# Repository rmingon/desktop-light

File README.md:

# Desktop Light

## desktop light with micro usb programming usb and extendable light

### features
* ESP32
* WS2812b
* RTC
* 3 programmable buttons
* CH310 usb programming
* Jack connector 5V

### Real

### 3d

### pcb

### schematic

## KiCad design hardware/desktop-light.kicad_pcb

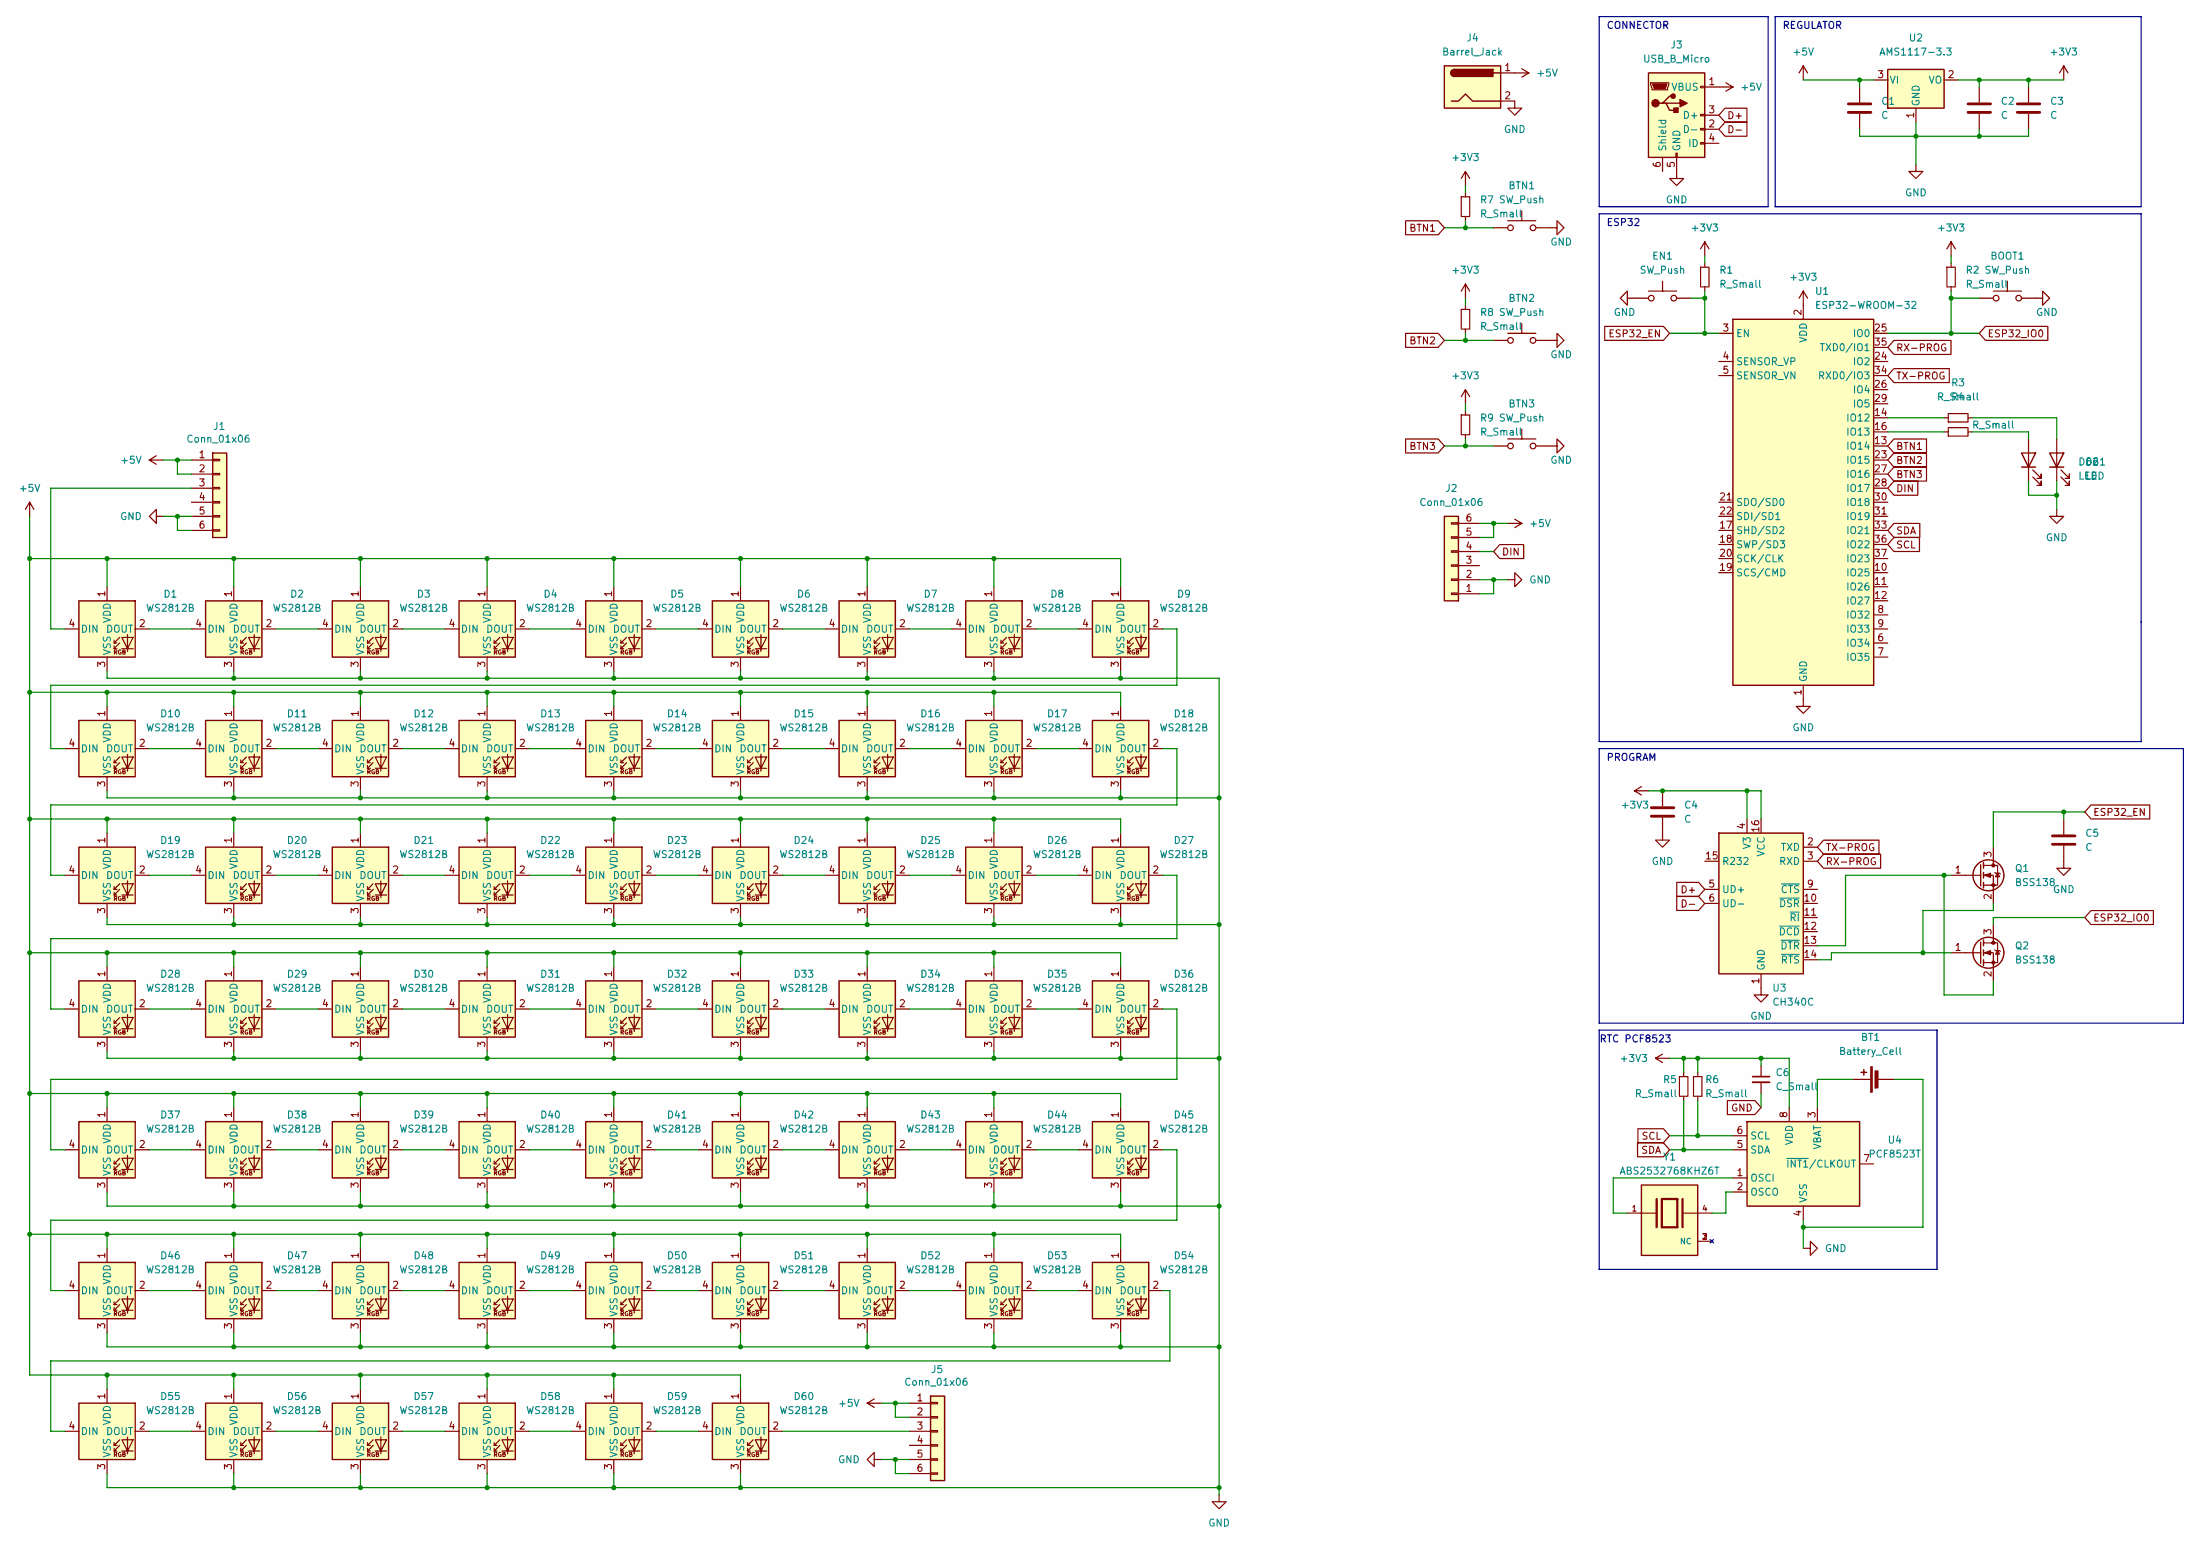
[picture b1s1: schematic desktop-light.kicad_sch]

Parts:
BOOT1: SW_Push; SW_SPST_FSMSM
BT1: Battery_Cell; BatteryHolder_LINX_BAT-HLD-012-SMT
BTN1, BTN2, BTN3: SW_Push; SW_SPST_FSMSM
C1, C2, C3, C4, C5: C; C_0603_1608Metric
C6: C_Small; C_0603_1608Metric
D1, D2, D3, D4, D5, D6, D7, D8, D9, D10, D11, D12, D13, D14, D15, D16, D17, D18, D19, D20, D21, D22, D23, D24, D25, D26, D27, D28, D29, D30, D31, D32, D33, D34, D35, D36, D37, D38, D39, D40, D41, D42, D43, D44, D45, D46, D47, D48, D49, D50, D51, D52, D53, D54, D55, D56, D57, D58, D59, D60: WS2812B; LED_WS2812B_PLCC4_5.0x5.0mm_P3.2mm
D61, D62: LED; LED_0603_1608Metric
EN1: SW_Push; SW_SPST_FSMSM
J1, J2, J5: Conn_01x06; JST_SH_BM06B-SRSS-TB_1x06-1MP_P1.00mm_Vertical
J3: USB_B_Micro; USB_Micro-B_Molex-105017-0001
J4: Barrel_Jack; BarrelJack_Wuerth_6941xx301002
Q1, Q2: BSS138; SOT-23
R1, R2, R3, R4, R5, R6, R7, R8, R9: R_Small; R_0603_1608Metric
U1: ESP32-WROOM-32
U2: AMS1117-3.3; SOT-223-3_TabPin2
U3: CH340C; SOIC-16_3.9x9.9mm_P1.27mm
U4: PCF8523T; SOIC-8_3.9x4.9mm_P1.27mm
Y1: ABS2532768KHZ6T; Crystal_SMD_Abracon_ABS25-4Pin_8.0x3.8mm; PARTREV 43738

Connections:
+3V3: C2.1, C3.1, C4.1, C6.1, R1.1, R2.1, R5.1, R6.1, R7.1, R8.1, R9.1, U1.2 (VDD), U2.2 (VO), U3.4 (V3), U3.16 (VCC), U4.8 (VDD)
+5V: C1.1, D1.1 (VDD), D2.1 (VDD), D3.1 (VDD), D4.1 (VDD), D5.1 (VDD), D6.1 (VDD), D7.1 (VDD), D8.1 (VDD), D9.1 (VDD), D10.1 (VDD), D11.1 (VDD), D12.1 (VDD), D13.1 (VDD), D14.1 (VDD), D15.1 (VDD), D16.1 (VDD), D17.1 (VDD), D18.1 (VDD), D19.1 (VDD), D20.1 (VDD), D21.1 (VDD), D22.1 (VDD), D23.1 (VDD), D24.1 (VDD), D25.1 (VDD), D26.1 (VDD), D27.1 (VDD), D28.1 (VDD), D29.1 (VDD), D30.1 (VDD), D31.1 (VDD), D32.1 (VDD), D33.1 (VDD), D34.1 (VDD), D35.1 (VDD), D36.1 (VDD), D37.1 (VDD), D38.1 (VDD), D39.1 (VDD), D40.1 (VDD), D41.1 (VDD), D42.1 (VDD), D43.1 (VDD), D44.1 (VDD), D45.1 (VDD), D46.1 (VDD), D47.1 (VDD), D48.1 (VDD), D49.1 (VDD), D50.1 (VDD), D51.1 (VDD), D52.1 (VDD), D53.1 (VDD), D54.1 (VDD), D55.1 (VDD), D56.1 (VDD), D57.1 (VDD), D58.1 (VDD), D59.1 (VDD), D60.1 (VDD), J1.1, J1.2, J2.5, J2.6, J3.1 (VBUS), J4.1, J5.1, J5.2, U2.3 (VI)
BTN1: BTN1.1, R7.2, U1.13 (IO14)
BTN2: BTN2.1, R8.2, U1.23 (IO15)
BTN3: BTN3.1, R9.2, U1.27 (IO16)
D+: J3.3 (D+), U3.5 (UD+)
D-: J3.2 (D-), U3.6 (UD-)
DIN: J2.4, U1.28 (IO17)
ESP32_EN: C5.1, EN1.2, Q1.3 (D), R1.2, U1.3 (EN)
ESP32_IO0: BOOT1.1, Q2.3 (D), R2.2, U1.25 (IO0)
GND: BOOT1.2, BT1.2 (-), BTN1.2, BTN2.2, BTN3.2, C1.2, C2.2, C3.2, C4.2, C5.2, C6.2, D1.3 (VSS), D2.3 (VSS), D3.3 (VSS), D4.3 (VSS), D5.3 (VSS), D6.3 (VSS), D7.3 (VSS), D8.3 (VSS), D9.3 (VSS), D10.3 (VSS), D11.3 (VSS), D12.3 (VSS), D13.3 (VSS), D14.3 (VSS), D15.3 (VSS), D16.3 (VSS), D17.3 (VSS), D18.3 (VSS), D19.3 (VSS), D20.3 (VSS), D21.3 (VSS), D22.3 (VSS), D23.3 (VSS), D24.3 (VSS), D25.3 (VSS), D26.3 (VSS), D27.3 (VSS), D28.3 (VSS), D29.3 (VSS), D30.3 (VSS), D31.3 (VSS), D32.3 (VSS), D33.3 (VSS), D34.3 (VSS), D35.3 (VSS), D36.3 (VSS), D37.3 (VSS), D38.3 (VSS), D39.3 (VSS), D40.3 (VSS), D41.3 (VSS), D42.3 (VSS), D43.3 (VSS), D44.3 (VSS), D45.3 (VSS), D46.3 (VSS), D47.3 (VSS), D48.3 (VSS), D49.3 (VSS), D50.3 (VSS), D51.3 (VSS), D52.3 (VSS), D53.3 (VSS), D54.3 (VSS), D55.3 (VSS), D56.3 (VSS), D57.3 (VSS), D58.3 (VSS), D59.3 (VSS), D60.3 (VSS), D61.1 (K), D62.1 (K), EN1.1, J1.5, J1.6, J2.1, J2.2, J3.5 (GND), J4.2, J5.5, J5.6, U1.1 (GND), U1.15 (GND), U1.38 (GND), U1.39 (GND), U2.1 (GND), U3.1 (GND), U4.4 (VSS)
unnamed: BT1.1 (+), U4.3 (VBAT)
unnamed: D1.4 (DIN), J1.3
unnamed: D1.2 (DOUT), D2.4 (DIN)
unnamed: D2.2 (DOUT), D3.4 (DIN)
unnamed: D3.2 (DOUT), D4.4 (DIN)
unnamed: D4.2 (DOUT), D5.4 (DIN)
unnamed: D5.2 (DOUT), D6.4 (DIN)
unnamed: D6.2 (DOUT), D7.4 (DIN)
unnamed: D7.2 (DOUT), D8.4 (DIN)
unnamed: D8.2 (DOUT), D9.4 (DIN)
unnamed: D9.2 (DOUT), D10.4 (DIN)
unnamed: D10.2 (DOUT), D11.4 (DIN)
unnamed: D11.2 (DOUT), D12.4 (DIN)
unnamed: D12.2 (DOUT), D13.4 (DIN)
unnamed: D13.2 (DOUT), D14.4 (DIN)
unnamed: D14.2 (DOUT), D15.4 (DIN)
unnamed: D15.2 (DOUT), D16.4 (DIN)
unnamed: D16.2 (DOUT), D17.4 (DIN)
unnamed: D17.2 (DOUT), D18.4 (DIN)
unnamed: D18.2 (DOUT), D19.4 (DIN)
unnamed: D19.2 (DOUT), D20.4 (DIN)
unnamed: D20.2 (DOUT), D21.4 (DIN)
unnamed: D21.2 (DOUT), D22.4 (DIN)
unnamed: D22.2 (DOUT), D23.4 (DIN)
unnamed: D23.2 (DOUT), D24.4 (DIN)
unnamed: D24.2 (DOUT), D25.4 (DIN)
unnamed: D25.2 (DOUT), D26.4 (DIN)
unnamed: D26.2 (DOUT), D27.4 (DIN)
unnamed: D27.2 (DOUT), D28.4 (DIN)
unnamed: D28.2 (DOUT), D29.4 (DIN)
unnamed: D29.2 (DOUT), D30.4 (DIN)
unnamed: D30.2 (DOUT), D31.4 (DIN)
unnamed: D31.2 (DOUT), D32.4 (DIN)
unnamed: D32.2 (DOUT), D33.4 (DIN)
unnamed: D33.2 (DOUT), D34.4 (DIN)
unnamed: D34.2 (DOUT), D35.4 (DIN)
unnamed: D35.2 (DOUT), D36.4 (DIN)
unnamed: D36.2 (DOUT), D37.4 (DIN)
unnamed: D37.2 (DOUT), D38.4 (DIN)
unnamed: D38.2 (DOUT), D39.4 (DIN)
unnamed: D39.2 (DOUT), D40.4 (DIN)
unnamed: D40.2 (DOUT), D41.4 (DIN)
unnamed: D41.2 (DOUT), D42.4 (DIN)
unnamed: D42.2 (DOUT), D43.4 (DIN)
unnamed: D43.2 (DOUT), D44.4 (DIN)
unnamed: D44.2 (DOUT), D45.4 (DIN)
unnamed: D45.2 (DOUT), D46.4 (DIN)
unnamed: D46.2 (DOUT), D47.4 (DIN)
unnamed: D47.2 (DOUT), D48.4 (DIN)
unnamed: D48.2 (DOUT), D49.4 (DIN)
unnamed: D49.2 (DOUT), D50.4 (DIN)
unnamed: D50.2 (DOUT), D51.4 (DIN)
unnamed: D51.2 (DOUT), D52.4 (DIN)
unnamed: D52.2 (DOUT), D53.4 (DIN)
unnamed: D53.2 (DOUT), D54.4 (DIN)
unnamed: D54.2 (DOUT), D55.4 (DIN)
unnamed: D55.2 (DOUT), D56.4 (DIN)
unnamed: D56.2 (DOUT), D57.4 (DIN)
unnamed: D57.2 (DOUT), D58.4 (DIN)
unnamed: D58.2 (DOUT), D59.4 (DIN)
unnamed: D59.2 (DOUT), D60.4 (DIN)
unnamed: D60.2 (DOUT), J5.3
unnamed: D61.2 (A), R4.2
unnamed: D62.2 (A), R3.2
unnamed: Q1.1 (G), Q2.2 (S), U3.13 (~DTR)
unnamed: Q1.2 (S), Q2.1 (G), U3.14 (~RTS)
unnamed: R3.1, U1.14 (IO12)
unnamed: R4.1, U1.16 (IO13)
unnamed: U4.1 (OSCI), Y1.1
unnamed: U4.2 (OSCO), Y1.4
RX-PROG: U1.35 (TXD0/IO1), U3.3 (RXD)
SCL: R6.2, U1.36 (IO22), U4.6 (SCL)
SDA: R5.2, U1.33 (IO21), U4.5 (SDA)
TX-PROG: U1.34 (RXD0/IO3), U3.2 (TXD)

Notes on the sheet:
ESP32
REGULATOR
CONNECTOR
PROGRAM
RTC PCF8523

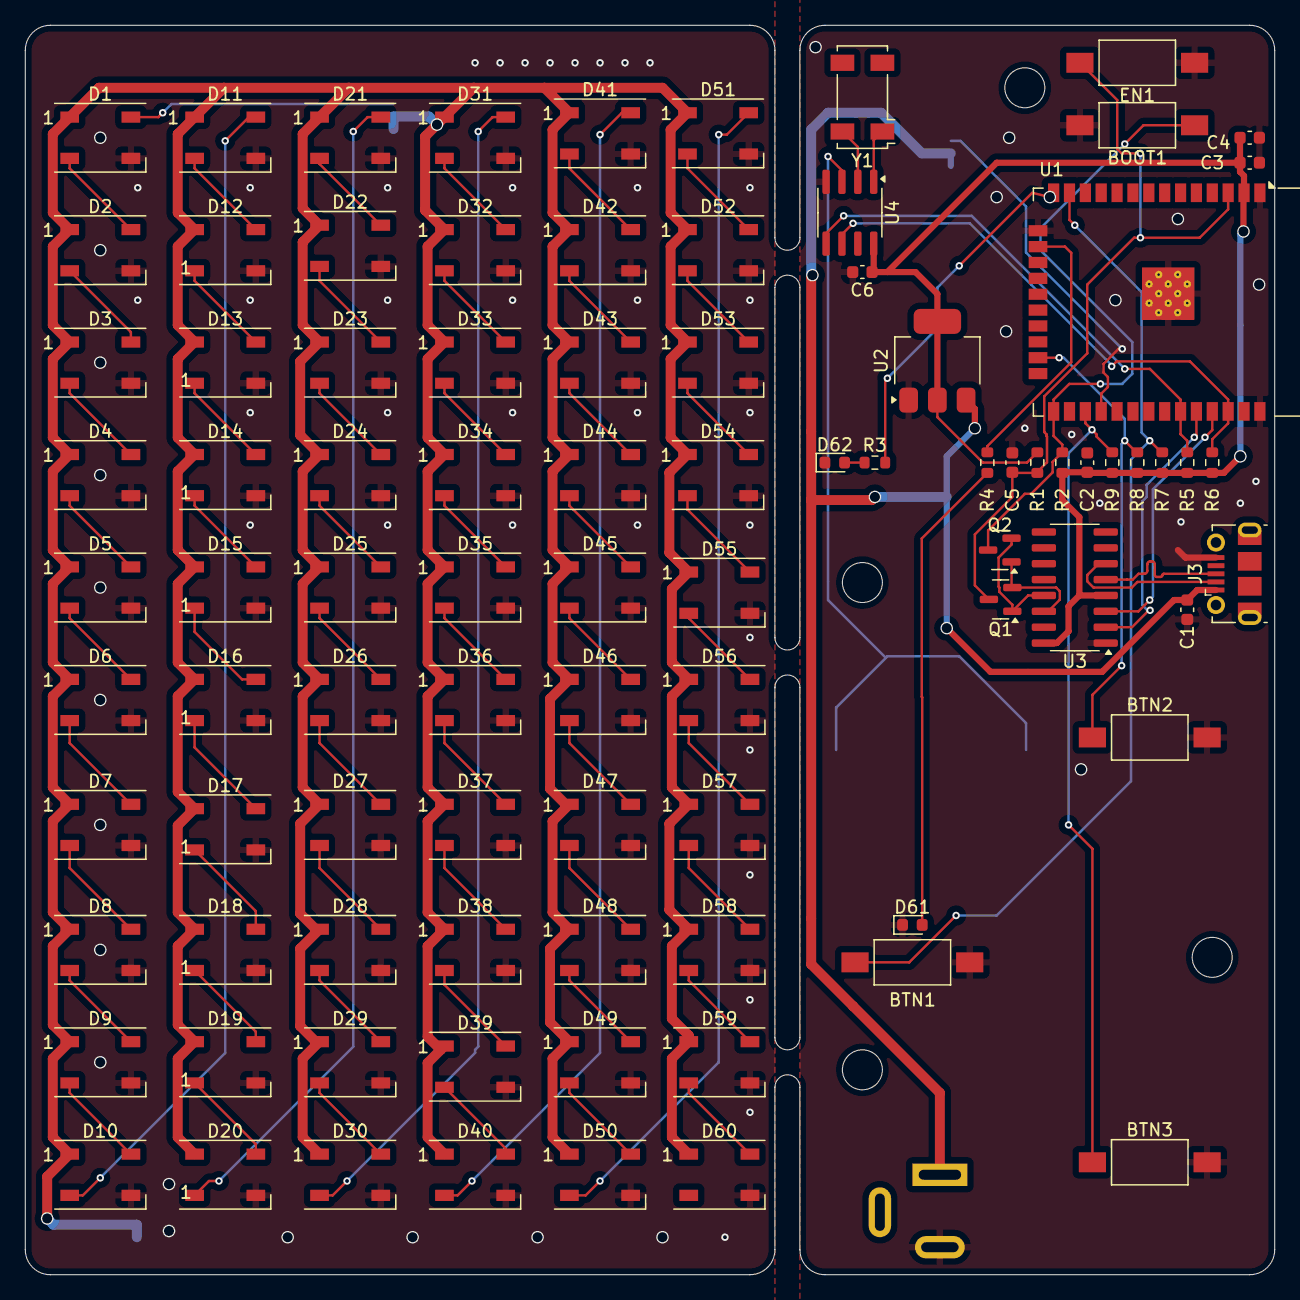
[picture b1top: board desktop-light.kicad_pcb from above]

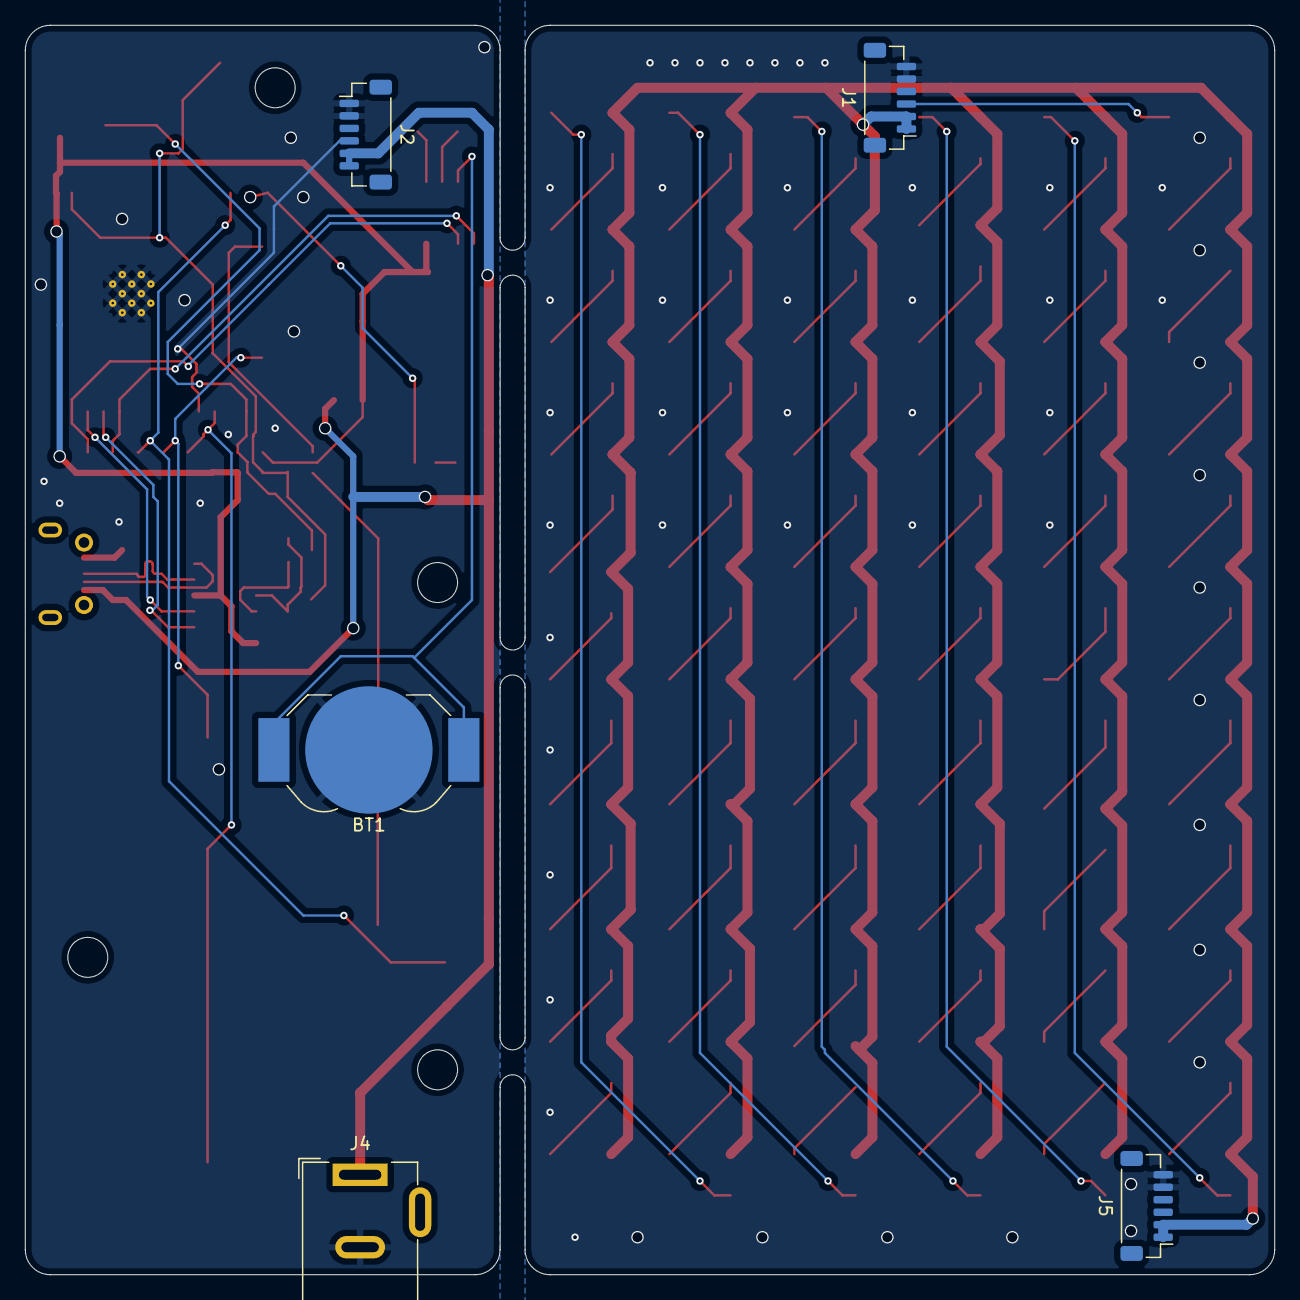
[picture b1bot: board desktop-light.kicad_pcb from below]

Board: 2 copper layers, 100.0 x 100.0 mm, 95 parts (5 on the bottom side), 85 nets.

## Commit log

2024-08-13 add leds
2024-08-13 led position
2024-08-13 add esp32
2024-08-14 add clock
2024-08-14 add pictures
2024-08-14 finish wiring
2024-08-14 add plot setting
2024-08-14 add vias
2025-01-16 add real photos
